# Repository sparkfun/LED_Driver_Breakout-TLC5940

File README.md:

SparkFun LED Driver Breakout -TLC5940
========================================

[*SparkFun LED Driver Breakout -TLC5940(BOB-10616)*](https://www.sparkfun.com/products/10616)

 The TLC5940 is a 16 channel PWM unit with 12 bit duty cycle control (0-4095), 6 bit current limit control (0-63), and a daisy chainable serial interface. 
 This breakout board is a good way to take full advantage of this useful IC. 
 All 16 PWM channels are broken out to standard 0.1" headers, which run alongside convenient voltage and ground rails.

Repository Contents
-------------------

* **/Firmware** - Example code. 
* **/Hardware** - Eagle design files (.brd, .sch)
* **/Libraries** - Libraries for use with the TLC5940.
* **/Production** - Production panel files (.brd)

Documentation
--------------
* **[Library](https://github.com/sparkfun/SparkFun_TLC5940_Arduino_Library)** - Arduino Library for the TLC5940.
* **[SparkFun Fritzing repo](https://github.com/sparkfun/Fritzing_Parts)** - Fritzing diagrams for SparkFun products.
* **[SparkFun 3D Model repo](https://github.com/sparkfun/3D_Models)** - 3D models of SparkFun products. 

Version History
---------------

* [v1.3](https://github.com/sparkfun/LED_Driver_Breakout-TLC5940/tree/V_H1.3_L1.0.1) - Hardware version 1.3. Currently live. 
* [v1.2](https://github.com/sparkfun/LED_Driver_Breakout-TLC5940/tree/V_H.1_L1.0.1) - Hardware version 1.2

License Information
-------------------
This product is _**open source**_! 

The **hardware** is released under [Creative Commons ShareAlike 4.0 International](https://creativecommons.org/licenses/by-sa/4.0/).

Please use, reuse, and modify these files as you see fit. Please maintain attribution to SparkFun Electronics and release anything derivative under the same license.

Distributed as-is; no warranty is given.

- Your friends at SparkFun.

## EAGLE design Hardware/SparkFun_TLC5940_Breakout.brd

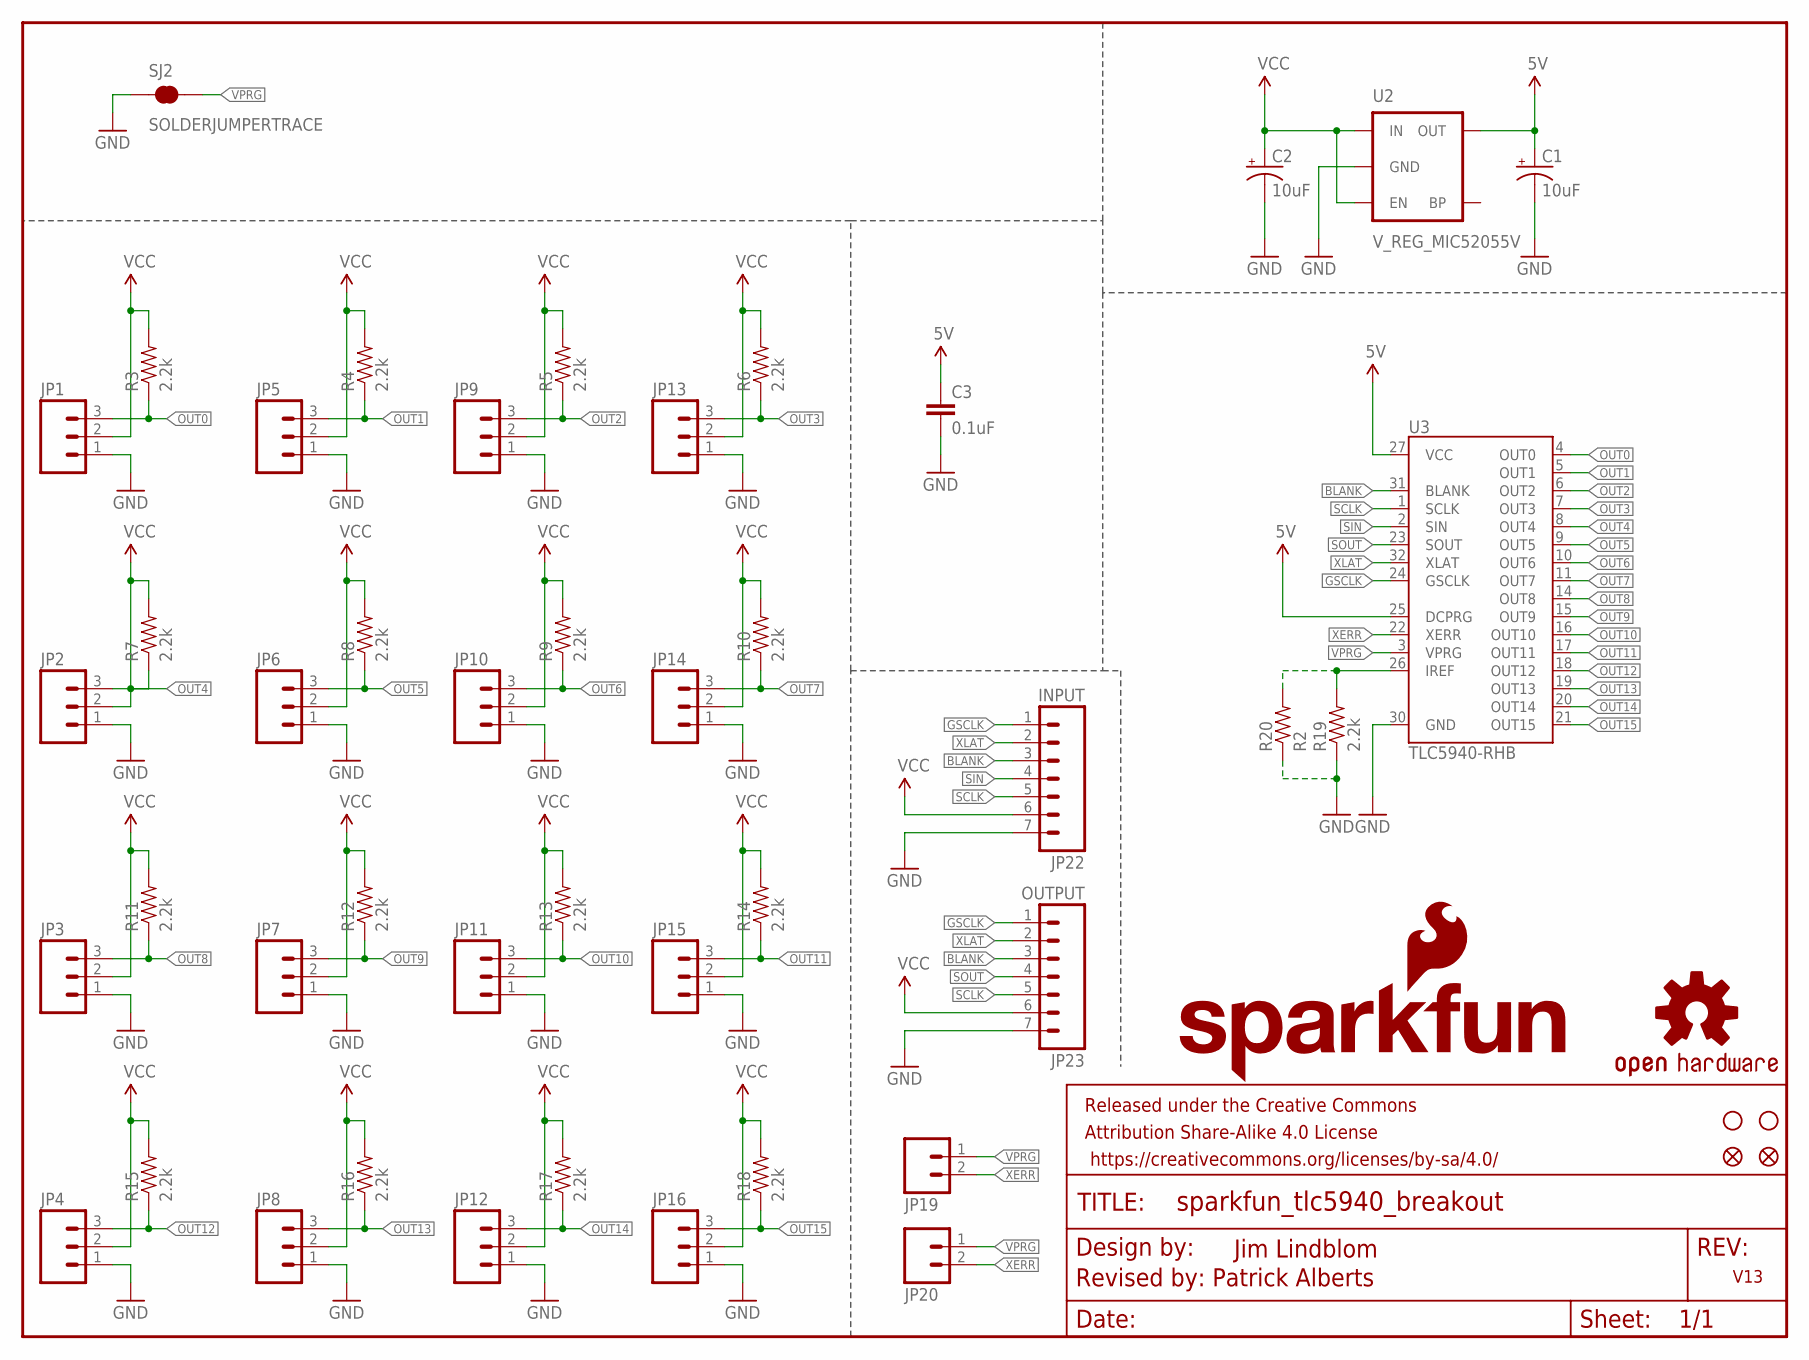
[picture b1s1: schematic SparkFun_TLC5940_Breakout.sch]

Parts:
C1: 10uF; EIA3216
C2: 10uF; EIA3528
C3: 0.1uF; 0603-CAP
FRAME1: FRAME-LETTER; CREATIVE_COMMONS
JP1, JP2, JP3, JP4, JP5, JP6, JP7, JP8, JP9, JP10, JP11, JP12, JP13, JP14, JP15, JP16: M03PTH; 1X03
JP17, JP18: STAND-OFF
JP19, JP20: M02PTH; 1X02
JP21, JP26: FIDUCIAL1X2; FIDUCIAL-1X2
JP22: INPUT; 1X07
JP23: OUTPUT; 1X07
LOGO1: OSHW-LOGOS; OSHW-LOGO-S
LOGO2: SFE_LOGO_NAME_FLAME.2_INCH; SFE_LOGO_NAME_FLAME_.2
R3, R4, R5, R6, R7, R8, R9, R10, R11, R12, R13, R14, R15, R16, R17, R18, R19: 2.2k; 0603-RES
R20: R2; AXIAL-0.3-KIT
SJ2: SOLDERJUMPERTRACE; SJ_2S-TRACE
U2: V_REG_MIC52055V; SOT23-5
U3: TLC5940-RHB; QFN-32

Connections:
5V: C1.A (+), C3.1, U2.5 (OUT), U3.25 (DCPRG), U3.27 (VCC)
BLANK: JP22.3, JP23.3, U3.31 (BLANK)
GND: C1.C (-), C2.C (-), C3.2, JP1.1, JP2.1, JP3.1, JP4.1, JP5.1, JP6.1, JP7.1, JP8.1, JP9.1, JP10.1, JP11.1, JP12.1, JP13.1, JP14.1, JP15.1, JP16.1, JP22.7, JP23.7, R19.1, R20.P$1 (1), SJ2.1, U2.2 (GND), U3.30 (GND)
GSCLK: JP22.1, JP23.1, U3.24 (GSCLK)
unnamed: R19.2, R20.P$2 (2), U3.26 (IREF)
OUT0: JP1.3, R3.1, U3.4 (OUT0)
OUT1: JP5.3, R4.1, U3.5 (OUT1)
OUT2: JP9.3, R5.1, U3.6 (OUT2)
OUT3: JP13.3, R6.1, U3.7 (OUT3)
OUT4: JP2.3, R7.1, U3.8 (OUT4)
OUT5: JP6.3, R8.1, U3.9 (OUT5)
OUT6: JP10.3, R9.1, U3.10 (OUT6)
OUT7: JP14.3, R10.1, U3.11 (OUT7)
OUT8: JP3.3, R11.1, U3.14 (OUT8)
OUT9: JP7.3, R12.1, U3.15 (OUT9)
OUT10: JP11.3, R13.1, U3.16 (OUT10)
OUT11: JP15.3, R14.1, U3.17 (OUT11)
OUT12: JP4.3, R15.1, U3.18 (OUT12)
OUT13: JP8.3, R16.1, U3.19 (OUT13)
OUT14: JP12.3, R17.1, U3.20 (OUT14)
OUT15: JP16.3, R18.1, U3.21 (OUT15)
SCLK: JP22.5, JP23.5, U3.1 (SCLK)
SIN: JP22.4, U3.2 (SIN)
SOUT: JP23.4, U3.23 (SOUT)
VCC: C2.A (+), JP1.2, JP2.2, JP3.2, JP4.2, JP5.2, JP6.2, JP7.2, JP8.2, JP9.2, JP10.2, JP11.2, JP12.2, JP13.2, JP14.2, JP15.2, JP16.2, JP22.6, JP23.6, R3.2, R4.2, R5.2, R6.2, R7.2, R8.2, R9.2, R10.2, R11.2, R12.2, R13.2, R14.2, R15.2, R16.2, R17.2, R18.2, U2.1 (IN), U2.3 (EN)
VPRG: JP19.1, JP20.1, SJ2.2, U3.3 (VPRG)
XERR: JP19.2, JP20.2, U3.22 (XERR)
XLAT: JP22.2, JP23.2, U3.32 (XLAT)

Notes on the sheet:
V13
Jim Lindblom
Revised by: Patrick Alberts

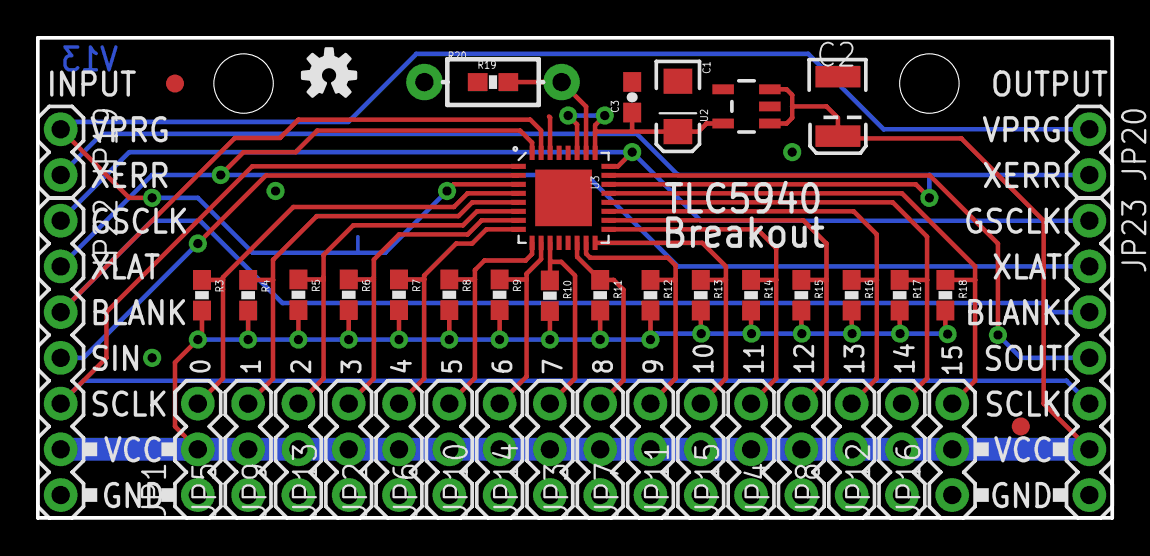
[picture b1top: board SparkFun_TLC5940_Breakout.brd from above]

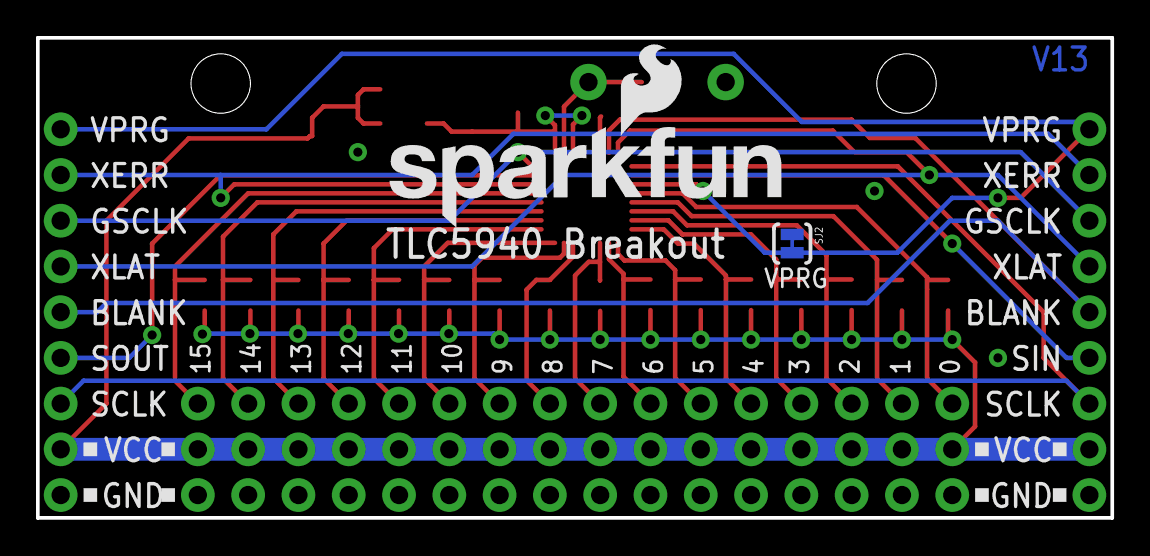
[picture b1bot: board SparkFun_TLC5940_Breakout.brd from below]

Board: 2 copper layers, 59.7 x 26.7 mm, 51 parts (2 on the bottom side), 28 nets.

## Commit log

2014-12-11 Initial Commit with BRD/SCH
2015-01-14 computer change
2015-01-29 Fixed sch issues, updated to 0603, minor re routes.
2015-02-02 Fixed QC Checklist issues
2015-04-28 Adding directories, necessary files
2015-04-29 Updating READMES
2015-04-29 Squashed 'Libraries/Arduino/' content from commit 09ea0f2
    git-subtree-dir: Libraries/Arduino
    git-subtree-split: 09ea0f29b5f23ba79426c3c33b837437829adf9c
2015-06-08 Squashed 'Libraries/Arduino/' changes from 09ea0f2..9c3856a
    git-subtree-dir: Libraries/Arduino
    git-subtree-split: 9c3856a03f593f756db51a219c9790652309ccf4
2015-06-08 Squashed 'Libraries/Arduino/' changes from 9c3856a..7814504
    7814504 Fixing library.properties file
    09ea0f2 Updating README with associated product links
    b5160be Adding license, updating README
    71a8aa8 Adding library files
    fd5b4cd Fixing formatting
    2eb5d6c Updating README with Arduino library specific documentation
2015-10-05 Squashed 'Libraries/Arduino/' changes from 7814504..7c3d8c7
    7c3d8c7 Fixing compilation error
    84f472c Fixing library.properties to enable loading in Arduino IDE
    git-subtree-dir: Libraries/Arduino
    git-subtree-split: 7c3d8c7861b762511ad4b3e899ffde8689cd396d
2016-01-11 Squashed 'Libraries/Arduino/' changes from 7c3d8c7..18a0c0f
    18a0c0f Updating file names for codebender fix
    git-subtree-dir: Libraries/Arduino
    git-subtree-split: 18a0c0fa8911f19f615ccea7981273a6ffd0adf4

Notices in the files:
parts and their libraries:
SparkFun-Capacitors: Licensing: Creative Commons ShareAlike 4.0 International - https://creativecommons.org/licenses/by-sa/4.0
SparkFun-Aesthetics: Released under the Creative Commons Attribution Share-Alike 4.0 License
SparkFun-Aesthetics: Released under the Creative Commons
